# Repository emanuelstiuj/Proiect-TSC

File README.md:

# OpenBook - E-Reader Project  
**Developed by Emanuel-Stefan Stiuj - TSC 2025**

The OpenBook is an innovative, open-source e-reader designed for low power consumption, expandability, and ease of use. Built around the ESP32-C6-WROOM-1-N8 microcontroller, this project integrates an e-paper display, environmental sensing, real-time clock functionality, and robust storage options into a portable, battery-powered device. This README provides a detailed breakdown of the hardware design, functionality, and implementation, ensuring all critical aspects are covered.

---

## Project Overview

OpenBook is a fully functional e-reader that leverages modern hardware to deliver a seamless reading experience. Key features include:
- A 7.5-inch e-paper display for crisp, low-power text rendering.
- Wi-Fi 6 and Bluetooth 5 connectivity via the ESP32-C6 for wireless content updates.
- SD card and external flash storage for e-books and logs.
- Environmental monitoring with the BME688 sensor (temperature, humidity, pressure, air quality).
- Precise timekeeping with the DS3231 RTC module.
- USB-C for power, charging, and data transfer, with a Li-Po battery for portability.
- Expandability through a Qwiic I²C connector.

The design prioritizes energy efficiency, modularity, and user interaction via three tactile buttons, making it ideal for avid readers and hardware enthusiasts alike.

---

## Hardware Architecture

The OpenBook hardware architecture integrates several key components powered through a USB-C input and a Li-Po battery. The system uses a battery charger (MCP73831) to manage the 2500mAh Li-Po battery, which supplies power to an LDO regulator outputting 3.3V. This voltage powers the ESP32-C6-WROOM-1-N8 microcontroller, a 7.5-inch e-paper display, an SD card module, a 64MB NOR Flash, a DS3231 RTC, a BME688 sensor, and a MAX17048 fuel gauge. The ESP32 connects to the display, SD card, and flash via SPI, to the RTC, sensor, and fuel gauge via I²C, and to three tactile buttons via GPIO. The USB-C also provides data connectivity, and a Qwiic connector enables I²C expansion.

---

## Hardware Components and Functionality

### 1. Main Microcontroller: ESP32-C6-WROOM-1-N8
- **Processor**: 32-bit RISC-V, up to 160 MHz.
- **Memory**: 512 KB SRAM + 64 MB external NOR Flash (W25Q512JVEIQ).
- **Connectivity**: Wi-Fi 6 (2.4 GHz), Bluetooth 5 LE, USB 2.0.
- **Interfaces**: SPI, I²C, UART, GPIO.
- **Power**: 3.3V via LDO; supports deep sleep for minimal power use (<10 µA).
- **Why Chosen?**: Offers robust wireless capabilities, ample GPIO, and low-power modes, perfect for an e-reader with connectivity needs.

### 2. E-Paper Display
- **Type**: 7.5-inch Waveshare e-ink display (800x480 resolution).
- **Interface**: 4-wire SPI (MOSI, SCK, CS, DC) + control signals (RST, BUSY).
- **Pins**:
  - `EPD_CS` → `IO10`
  - `EPD_DC` → `IO5`
  - `EPD_RST` → `IO23`
  - `EPD_BUSY` → `IO3`
  - Shared SPI: `MOSI` (`IO7`), `SCK` (`IO6`).
- **Power**: 3.3V, ~20-50 mA during refresh, near-zero in static mode.
- **Why Chosen?**: E-paper’s ultra-low static power consumption makes it ideal for prolonged reading without draining the battery.

### 3. Storage
- **SD Card Module**:
  - **Interface**: SPI.
  - **Pins**: `SS_SD` → `IO4`, `MOSI` → `IO7`, `MISO` → `IO2`, `SCK` → `IO6`.
  - **Purpose**: External storage for e-books and firmware updates.
- **External Flash (W25Q512JVEIQ)**:
  - **Interface**: SPI (Quad I/O).
  - **Pins**: `FLASH_CS` → `IO11`, shared `MOSI`, `MISO`, `SCK`.
  - **Capacity**: 64 MB for firmware and content.
- **Power**: Both operate at 3.3V, with ~10-100 mA during active use.

### 4. Real-Time Clock (RTC): DS3231SN
- **Interface**: I²C.
- **Pins**: `SDA` → `IO21`, `SCL` → `IO22`, `INT_RTC` → `IO8`, `32KHZ` → `IO1`, `RTC_RST` → `IO18`.
- **Power**: 3.3V, <1 µA with backup (super-capacitor or coin cell).
- **Why Chosen?**: Provides accurate timekeeping, critical for timestamped logs or scheduled tasks, even when powered off.

### 5. Environmental Sensor: BME688
- **Measurements**: Temperature, humidity, pressure, VOC/eCO2.
- **Interface**: I²C (shared bus with RTC and Fuel Gauge).
- **Pins**: `SDA` → `IO21`, `SCL` → `IO22`.
- **Power**: 3.3V, ~0.8-3.6 mA active, <1 µA in sleep.
- **Why Chosen?**: Enhances user experience by monitoring reading conditions.

### 6. Power Management
- **Battery**: 2500 mAh Li-Po (3.7V nominal).
- **Charger**: MCP73831, charges via USB-C at up to 1A.
- **Fuel Gauge**: MAX17048, I²C (`SDA`/`SCL`), monitors battery level (~50 µA).
- **LDO Regulator**: XC6220A331MR-G, steps 5V down to 3.3V for all components.
- **USB-C**: Power input (5V) and data (USB_D+ → `IO13`, USB_D- → `IO12`).
- **Protection**: Reverse polarity diodes, ESD protection (USBLC6-2SC6Y).

---

## Communication Interfaces

| Interface | Components             | ESP32-C6 Pins                   | Notes                       |
|-----------|------------------------|---------------------------------|-----------------------------|
| SPI       | E-Paper, SD Card, Flash| `MOSI` (`IO7`), `MISO` (`IO2`), `SCK` (`IO6`) | Shared bus with individual CS pins. |
| I²C       | RTC, BME688, Fuel Gauge| `SDA` (`IO21`), `SCL` (`IO22`) | 400 kHz bus, pull-ups included. |
| UART      | Debugging              | `TXD0`, `RXD0` (test pads)     | Optional, for development.  |
| GPIO      | Buttons, Status        | `IO0`-`IO23`                   | Flexible assignments.       |
| USB       | Power/Data             | `USB_D+` (`IO13`), `USB_D-` (`IO12`) | USB 2.0 full-speed.   |

---

## Power Consumption

| Component           | Typical Current (mA) | Notes                              |
|---------------------|----------------------|------------------------------------|
| ESP32-C6 (Idle)     | ~10                  | <10 µA in deep sleep.             |
| ESP32-C6 (Wi-Fi)    | 80-160               | Peak during wireless activity.    |
| E-Paper (Refresh)   | 20-50                | Near-zero when static.            |
| SD Card             | 30-100               | Active during read/write.         |
| Flash (NOR)         | 10-20                | Intermittent use.                 |
| BME688              | ~0.8-3.6             | <1 µA in sleep.                   |
| DS3231 RTC          | ~0.2-3.5             | <1 µA with backup.                |
| MAX17048            | ~0.05                | Continuous monitoring.            |
| **Total (Typical)** | **150-250 mA**       | Varies with usage; ~50 µA in sleep. |

**Battery Life**: With a 2500 mAh battery, OpenBook can last weeks in typical use (mostly static display) or hours during heavy Wi-Fi and refresh activity.

---

| **Component Name**                     | **Component Type**        | **Link** |
|----------------------------------------|--------------------------------------|----------|
| MicroSD_112ATA                         | microSD                              | [Attend SnapEDA](https://www.snapeda.com/parts/112A-TAAR-R03/Attend/view-part/) |
| LED_ADAFRUIT0603                       | LED                                  | [Kingbright SnapEDA](https://www.snapeda.com/parts/KP-1608SURCK/Kingbright/view-part/?ref=search&t=LED%200603) |
| CAP_CPH3225                            | C                                    | [Seiko SnapEDA](https://www.snapeda.com/parts/CPH3225A/Seiko/view-part/) |
| VREG_XC6220A                           | Voltage Regulator                    | [Torex Mouser](https://ro.mouser.com/ProductDetail/Torex-Semiconductor/XC6220A331MR-G?qs=AsjdqWjXhJ8ZSWznL1J0gg%3D%3D&utm_source=octopart&utm_medium=aggregator&utm_campaign=865-XC6220A331MR-G&utm_content=Torex%20Semiconductor) |
| FUEL_MAX17048                          | Cell Fuel Gauge with ModelGauge      | [Analog Devices SnapEDA](https://www.snapeda.com/parts/MAX17048G+T10/Analog%20Devices/view-part/) |
| ESP32C6_MODULE                         | ESP32                                | [Espressif SnapEDA](https://www.snapeda.com/parts/ESP32-C6-WROOM-1-N8/Espressif%20Systems/view-part/?ref=search&t=ESP32-C6-WROOM-1-N8) |
| DIODE_MBR0530                          | Diode Schottky                       | [Onsemi SnapEDA](https://www.snapeda.com/parts/MBR0530/Onsemi/view-part/) |
| BME680_SENSOR                          | Env Sensor                           | [Bosch SnapEDA](https://www.snapeda.com/parts/BME680/Bosch%20Sensortec/view-part/?ref=search&t=bme680) |
| INDUCTOR_744043                        | L                                    | [Wurth Mouser](https://eu.mouser.com/ProductDetail/Wurth-Elektronik/744043680?qs=PGXP4M47uW6VkZq%252BkzjrHA%3D%3D) |
| CONNECTOR_QWIIC                        | PRT-14417 QWIIC_CONNECTOR            | [SparkFun SnapEDA](https://www.snapeda.com/parts/PRT-14417/SparkFun/view-part/) |
| VARSISTOR_ESP                          | Varsistor (B72520T0350K062)          | [TDK Mouser](https://ro.mouser.com/ProductDetail/EPCOS-TDK/B72520T0350K062?qs=dEfas%2FXlABIszF52uu7vrg%3D%3D) |
| RES_RCL0402                            | R                                    | [YAGEO ComponentSearch](https://componentsearchengine.com/part-view/R0402%201%25%20100%20K%20(RC0402FR-07100KL)/YAGEO) |
| TVS_PGB1010603                         | Ipp Tvs Diode Surface Mount 0603     | [Littelfuse SnapEDA](https://www.snapeda.com/parts/PGB1010603MR/Littelfuse/view-part/) |
| MOSFET_SI1308                          | MOSFET Transistor                    | [Vishay SnapEDA](https://www.snapeda.com/parts/SI1308EDL-T1-GE3/Vishay/view-part/) |
| BUTTON_EVQP7                           | Button                               | [SnapEDA Button](https://www.snapeda.com/search/?q=EVQP7L01P&search-type=parts) |
| USBLC6_TVS                             | Ipp Tvs Diode Surface Mount          | [STMicro SnapEDA](https://www.snapeda.com/parts/USBLC6-2SC6Y/STMicroelectronics/view-part/?ref=dk&t=USBLC6-2SC6Y&con_ref=None) |
| FLASH_W25Q512                          | FLASH - NOR Memory                   | [Winbond SnapEDA](https://www.snapeda.com/parts/W25Q512JVEIQ/Winbond%20Electronics/view-part/?ref=search&t=W25Q512JVEIQ) |
| CAP_ESP32C0402                         | C                                    | [YAGEO ComponentSearch](https://componentsearchengine.com/part-view/CC0402MRX5R5BB106/YAGEO) |
| RTC_DS3231                             | I²C-Integrated RTC/TCXO/Crystal      | [Analog Devices SnapEDA](https://www.snapeda.com/parts/DS3231SN%23/Analog%20Devices/view-part/?ref=search&t=DS3231SN%23) |
| VDET_BD5229                            | Voltage Detector                     | [Rohm SnapEDA](https://www.snapeda.com/parts/BD5229G-TR/Rohm/view-part/?ref=search&t=BD5229G-TR) |
| SCHOTTKY_SD0805                        | Diode Schottky                       | [AVX ComponentSearch](https://componentsearchengine.com/part-view/SD0805S020S1R0/Kyocera%20AVX) |
| MOSFET_DMG2305                         | T DMG2305UX-7                        | [Diodes ComponentSearch](https://componentsearchengine.com/part-view/DMG2305UX-7/Diodes%20Incorporated) |
| CHARGE_MCP73831                        | Tiny Integrated Li-Ion/Li-Poly Charge Mgnt Controller | [Microchip ComponentSearch](https://componentsearchengine.com/part-view/MCP73831T-2ACI%2FOT/Microchip) |
| CONNECTOR_FH34SRJ                      | FH34SRJ-24S-0.5SH(99)               | [Hirose ComponentSearch](https://componentsearchengine.com/part-view/FH34SRJ-24S-0.5SH(99)/Hirose) |
| USB4110_GF                             | USB4110-GF-A                         | [GCT SnapEDA](https://www.snapeda.com/parts/USB4110-GF-A./Global%20Connector%20Technology/view-part/) |
| CAP_RCLPOL                             | C pol                                | [GrabCAD Tantalum](https://grabcad.com/library/tantalum-smd-capacitor-type-b-3528-1) |
| JUMPER_SJ                              | Jumper-SolderPasteJumper3way         | [GrabCAD Jumper](https://grabcad.com/library/solder-jumpers-1) |

---

## ESP32-C6 Pin Assignments

| Pin    | Signal       | Function                          | Reason for Assignment                  |
|--------|--------------|-----------------------------------|----------------------------------------|
| EN     | RESET        | System reset                     | Standard reset pin for ESP32.          |
| IO0    | INT_RTC      | RTC interrupt                    | Low-power interrupt capability.        |
| IO1    | 32KHZ        | 32 kHz RTC clock output          | Drives accurate timekeeping.           |
| IO2    | MISO         | SPI data input (SD/Flash/Display)| Shared SPI bus input.                  |
| IO3    | EPD_BUSY     | E-Paper busy status              | Monitors display readiness.            |
| IO4    | SS_SD        | SD Card chip select              | Dedicated CS for SD card.              |
| IO5    | EPD_DC       | E-Paper data/command             | Distinguishes data vs. commands.       |
| IO6    | SCK          | SPI clock                        | Shared SPI clock signal.               |
| IO7    | MOSI         | SPI data output                  | Shared SPI output for peripherals.     |
| IO9    | IO/BOOT      | Boot button                      | Triggers boot mode or power-on.        |
| IO10   | EPD_CS       | E-Paper chip select              | Dedicated CS for display.              |
| IO11   | FLASH_CS     | Flash chip select                | Dedicated CS for NOR Flash.            |
| IO12   | USB_D-       | USB differential data -          | Fixed USB pin.                         |
| IO13   | USB_D+       | USB differential data +          | Fixed USB pin.                         |
| IO15   | IO/CHANGE    | Page change button               | User input for navigation.             |
| IO18   | RTC_RST      | RTC reset                        | Hardware reset for RTC.                |
| IO21   | SDA          | I²C data line                    | Shared I²C bus for sensors/RTC.        |
| IO22   | SCL          | I²C clock line                   | Shared I²C clock signal.               |
| IO23   | EPD_RST      | E-Paper reset                    | Hardware reset for display.            |
| TXD0   | TX           | UART transmit (debug)            | Test pad for debugging.                |
| RXD0   | RX           | UART receive (debug)             | Test pad for debugging.                |

---

## Design Decisions

1. **Power Routing**: Power traces were prioritized and routed manually to ensure stability, followed by autorouting for signal lines.
2. **USB-C Integration**: Modified to avoid DRC errors, supporting both power and data seamlessly.
3. **E-Paper Choice**: Selected for its low power and readability, with a dedicated 3.3V supply controlled via a MOSFET (`EPD_3v3_c`) for efficiency.
4. **Modularity**: Qwiic connector and test pads enhance expandability and debuggability.
5. **ESD Protection**: Added to SPI, USB, and power lines to ensure durability.

---

## Implementation Steps

1. **Schematic Design**: Created in Autodesk Fusion, integrating all components with clear pin mappings.
2. **PCB Layout**: 
   - Defined GND plane and power net classes.
   - Applied custom routing rules for signal integrity.
   - Adjusted enclosure dimensions to fit the PCB.
3. **3D Modeling**: Designed battery and display mounts based on datasheets.
4. **Testing**: Used test pads for UART debugging and verified functionality.

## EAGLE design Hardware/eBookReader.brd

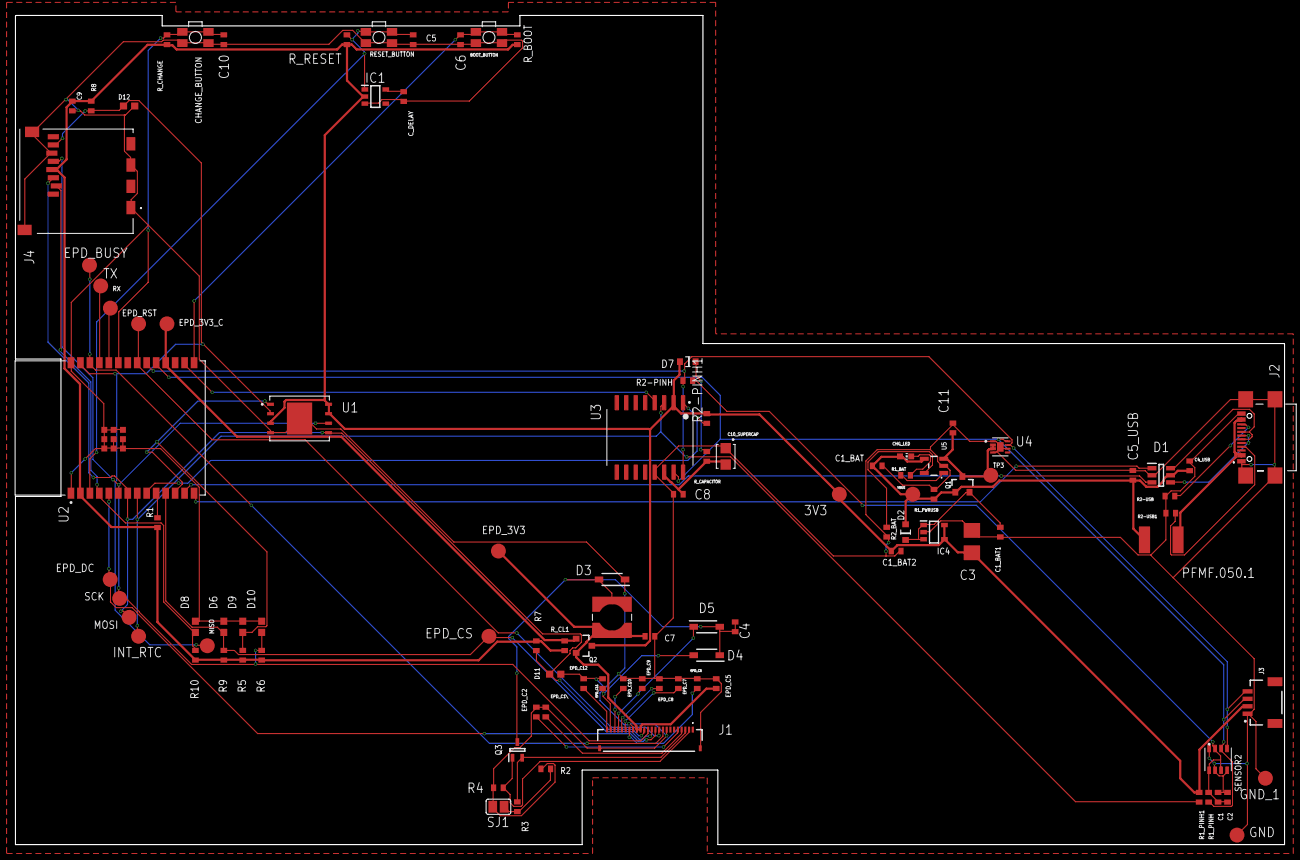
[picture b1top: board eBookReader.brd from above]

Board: 2 copper layers, 170.2 x 111.2 mm, 103 parts (0 on the bottom side), 54 nets.

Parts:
3V3: TPTP20R; TP20R
BOOT_BUTTON: BOOT_BUTTON; MYBUTTON
C1, C2, C4_USB, C6, C8, C9, C10: 100nF; ESP32_WROVER_EAGLE-LTSPICE_C0402
C1_BAT, C1_BAT1, C1_BAT2, C5_USB, C11: 4.7uF; ESP32_WROVER_EAGLE-LTSPICE_C0402
C3: 100uF TANT; RCL_CT3528
C4: 4.7uF/25V; ESP32_WROVER_EAGLE-LTSPICE_C0402
C5: 1uF; ESP32_WROVER_EAGLE-LTSPICE_C0402
C7: 10uF; ESP32_WROVER_EAGLE-LTSPICE_C0402
C10_SUPERCAP: CPH3225ACPH; CAPCP3225X100N
CHANGE_BUTTON: CHANGE_BUTTON; MYBUTTON
CHG_LED: ADAFRUIT_CHIP-LED0603
C_DELAY: 100nF; ESP32_WROVER_EAGLE-LTSPICE_C0402
D1: USBLC6-2SC6Y; SOT95P280X145-6N
D2: SD0805S020S1R0; ESP32_WROVER_AVX---SD0805S020S1R0_AVX_SD0805S020S1R0_0
D3, D4, D5: MBR0530; SOD3716X135N
D6, D8, D9, D10, D11, D12: PGB1010603MR; DIOC1608X36N
D7: ESP32_WROVER_AVX---SD0805S020S1R0_AVX_SD0805S020S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; ESP32_WROVER_AVX---SD0805S020S1R0_AVX_SD0805S020S1R0_0
EPD_3V3, EPD_3V3_C: TPTP20R; TP20R
EPD_BUSY: TPTP20R; TP20R
EPD_C1\, EPD_C2, EPD_C6, EPD_C7, EPD_C8, EPD_C9, EPD_C10, EPD_C11, EPD_C12: 1uF/50V; ESP32_WROVER_EAGLE-LTSPICE_C0402
EPD_C5: 0.1uF/50V; ESP32_WROVER_EAGLE-LTSPICE_C0402
EPD_CS: TPTP20R; TP20R
EPD_DC: TPTP20R; TP20R
EPD_RST: TPTP20R; TP20R
GND: TPTP20R; TP20R
GND_1: TPTP20R; TP20R
IC1: BD5229G-TR; SOT95P280X125-5N
IC4: XC6220A331MR-G; SOT95P280X120-5N
INT_RTC: TPTP20R; TP20R
J1: FH34SRJ-24S-0.5SH_99_FH34; FH34SRJ24S05SH99
J2: SAMACSYS_PARTS_USB4110-GF-A; SAMACSYS_PARTS_USB4110GFA
J3: QWIIC_RIGHT_ANGLE; JST04_1MM_RA
J4: 112A-TAAR-R03_ATTEND; 112ATAARR03ATTEND
L1: 68uH; IND_4828-WE-TPC_WRE
MISO: TPTP20R; TP20R
MOSI: TPTP20R; TP20R
PFMF.050.1: ESP32C6_VARISTOR; ESP32C6_VARISTOR_CT/CN1812
Q1, Q2: 20V/4.2A/52mΩ/1.4W; ESP32_WROVER_SPARKFUN-DISCRETESEMI_SOT23-3
Q3: SI1308EDL-T1-GE3; SOT65P210X110-3N
R1, R1_PINH, R1_PINH1, R2-PINH, R2-PINH1, R4, R5, R6, R7, R8, R9, R10: 10K; ESP32_WROVER_EAGLE-LTSPICE_R0402
R1_BAT: 200; ESP32_WROVER_EAGLE-LTSPICE_R0402
R1_PWRUSB: 100K; ESP32_WROVER_EAGLE-LTSPICE_R0402
R2: 2.2; ESP32_WROVER_EAGLE-LTSPICE_R0402
R2-USB, R2-USB1: 5k1; ESP32_WROVER_EAGLE-LTSPICE_R0402
R2_BAT: 2K; ESP32_WROVER_EAGLE-LTSPICE_R0402
R3: 0.47; ESP32_WROVER_EAGLE-LTSPICE_R0402
RESET_BUTTON: RESET_BUTTON; MYBUTTON
RX: TPTP20R; TP20R
R_BOOT: 10K; ESP32_WROVER_EAGLE-LTSPICE_R0402
R_CAPACITOR: 15; ESP32_WROVER_EAGLE-LTSPICE_R0402
R_CHANGE: 10K; ESP32_WROVER_EAGLE-LTSPICE_R0402
R_CL1: 10K; ESP32_WROVER_EAGLE-LTSPICE_R0402
R_RESET: 10K; ESP32_WROVER_EAGLE-LTSPICE_R0402
SCK: TPTP20R; TP20R
SENSOR2: BME688; ESP32_WROVER_BME680_PSON80P300X300X100-8N
SJ1: SJ
TP3: TPTP20R; TP20R
TX: TPTP20R; TP20R
U1: W25Q512JVEIQ; SON127P600X800X80-9N
U2: ESP32-C6-WROOM-1-N8; XCVR_ESP32-C6-WROOM-1-N8
U3: DS3231SN#; SOIC127P1032X265-16N
U4: MAX17048G+T10; SON50P200X200X80-9N
U5: MCP73831; ESP32_WROVER_SPARKFUN-IC-POWER_SOT23-5
VBUS: TPTP20R; TP20R

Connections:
3V3: 3V3.TP, C1_BAT2.1, C3.+, C9.1, D7.2, IC1.2, IC4.4, IC4.5, J3.2, J4.P4, Q2.3, R1.1, R1_PINH1.2, R2-PINH1.2, R5.2, R6.2, R7.2, R8.2, R9.2, R10.2, R_BOOT.1, R_CHANGE.1, R_CL1.1, R_RESET.1, U1.3, U1.7, U1.8, U2.2, U3.2
12C_PW: C1.1, C2.1, R1_PINH.2, R2-PINH.2, SENSOR2.2, SENSOR2.6, SENSOR2.8
32KHZ: R2-PINH1.1, U2.9, U3.1
DN: D1.4, J2.A7, J2.B7
DP: D1.6, J2.A6, J2.B6
EPD_3V3: C7.1, EPD_3V3.TP, EPD_C5.1, J1.15, J1.16, L1.2, Q2.2
EPD_3V3_C: EPD_3V3_C.TP, Q2.1, R_CL1.2, U2.18
EPD_BUSY: EPD_BUSY.TP, J1.9, U2.26
EPD_CS: D6.1, EPD_CS.TP, J1.12, R9.1, U2.11
EPD_DC: EPD_DC.TP, J1.11, U2.5
EPD_RST: EPD_RST.TP, J1.10, U2.21
FLASH_CS: D9.1, R5.1, U1.1, U2.12
GDR: J1.2, Q3.1, R4.1
GND: BOOT_BUTTON.1, BOOT_BUTTON.2, C1.2, C1_BAT.2, C1_BAT1.2, C1_BAT2.2, C2.2, C3.-, C4_USB.2, C5.2, C5_USB.2, C6.2, C7.2, C8.2, C9.2, C10.2, C10_SUPERCAP.1, C11.2, CHANGE_BUTTON.1, CHANGE_BUTTON.2, C_DELAY.2, D1.2, D3.1, D6.2, D8.2, D9.2, D10.2, D11.2, D12.2, EPD_C1\.2, EPD_C2.2, EPD_C5.2, EPD_C6.2, EPD_C7.2, EPD_C8.2, EPD_C9.2, EPD_C10.2, EPD_C11.2, EPD_C12.2, GND.TP, GND_1.TP, IC1.3, IC4.2, J1.8, J1.17, J1.MP1, J1.MP2, J2.A1, J2.A12, J2.B1, J2.B12, J2.MP1, J2.MP2, J2.MP3, J2.MP4, J3.1, J4.G1, J4.G2, J4.G3, J4.G4, J4.P6, R1_PWRUSB.1, R2.1, R2-USB.2, R2-USB1.1, R2_BAT.1, R4.2, RESET_BUTTON.1, RESET_BUTTON.2, SENSOR2.1, SENSOR2.5, SENSOR2.7, SJ1.1, U1.4, U1.9, U2.1, U2.28, U2.29_1, U2.29_2, U2.29_3, U2.29_4, U2.29_5, U2.29_6, U2.29_7, U2.29_8, U2.29_9, U3.13, U4.1, U4.4, U4.6, U4.9, U5.2
GPIO8: R1.2, U2.10
INT_RTC: INT_RTC.TP, R1_PINH1.1, U2.8, U3.3
IO/BOOT: BOOT_BUTTON.3, BOOT_BUTTON.4, C6.1, R_BOOT.2, U2.15
IO/CHANGE: C10.1, CHANGE_BUTTON.3, CHANGE_BUTTON.4, R_CHANGE.2, U2.23
MISO: D12.1, J4.P7, MISO.TP, R8.1, U1.2, U2.27
MOSI: D11.1, J1.14, J4.P3, MOSI.TP, R7.1, U1.5, U2.7
unnamed: D7.1, R_CAPACITOR.2
unnamed: EPD_C1\.1, J1.4
unnamed: EPD_C8.1, J1.20
unnamed: EPD_C2.1, J1.5
unnamed: EPD_C6.1, J1.18
unnamed: C_DELAY.1, IC1.5
unnamed: EPD_C7.1, J1.19
unnamed: EPD_C12.1, J1.24
unnamed: EPD_C10.1, J1.22
unnamed: J2.B5, R2-USB.1
unnamed: C1_BAT1.1, D2.1, IC4.1, IC4.3, Q1.2
unnamed: R2_BAT.2, U5.5
unnamed: R1_BAT.1, U5.1
unnamed: J2.A5, R2-USB1.2
unnamed: CHG_LED.C, R1_BAT.2
PREVGH: D5.1, EPD_C9.1, J1.21
PREVGL: D4.2, EPD_C11.1, J1.23
RESE: J1.3, Q3.2, R3.1
RESE': R2.2, R3.2, SJ1.2
RESET: C5.1, IC1.1, RESET_BUTTON.3, RESET_BUTTON.4, R_RESET.2, U2.3
RTC_RST: U2.16, U3.4
RX: RX.TP, U2.24
SCK: D10.1, J1.13, J4.P5, R6.1, SCK.TP, U1.6, U2.6
SCL: J3.4, R2-PINH.1, SENSOR2.4, U2.20, U3.16, U4.7
SDA: J3.3, R1_PINH.1, SENSOR2.3, U2.19, U3.15, U4.8
SRC: C4.1, C4.2, D3.2, D4.1, D5.2, L1.1, Q3.3
SS_SD: D8.1, J4.P2, R10.1, U2.4
TX: TX.TP, U2.25
USB_D+: D1.1, U2.14
USB_D-: D1.3, U2.13
VBAT: C11.1, Q1.3, TP3.TP, U4.2, U4.3, U5.3
VBUS: C1_BAT.1, C4_USB.1, C5_USB.1, CHG_LED.A, D1.5, D2.2, PFMF.050.1.2, Q1.1, R1_PWRUSB.2, U5.4, VBUS.TP
VRTC: C8.1, C10_SUPERCAP.2, R_CAPACITOR.1, U3.14
VUSB: J2.A4, J2.A9, J2.B4, J2.B9, PFMF.050.1.1

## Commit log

2025-03-17 Added README file
2025-04-05 Added all the files
2025-04-06 Changed .f3z file
2025-04-13 Updated eBookReader.brd

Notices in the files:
parts and their libraries:
COPYRIGHT: Copyright (C) 2024 Ultra Librarian. All rights reserved.
